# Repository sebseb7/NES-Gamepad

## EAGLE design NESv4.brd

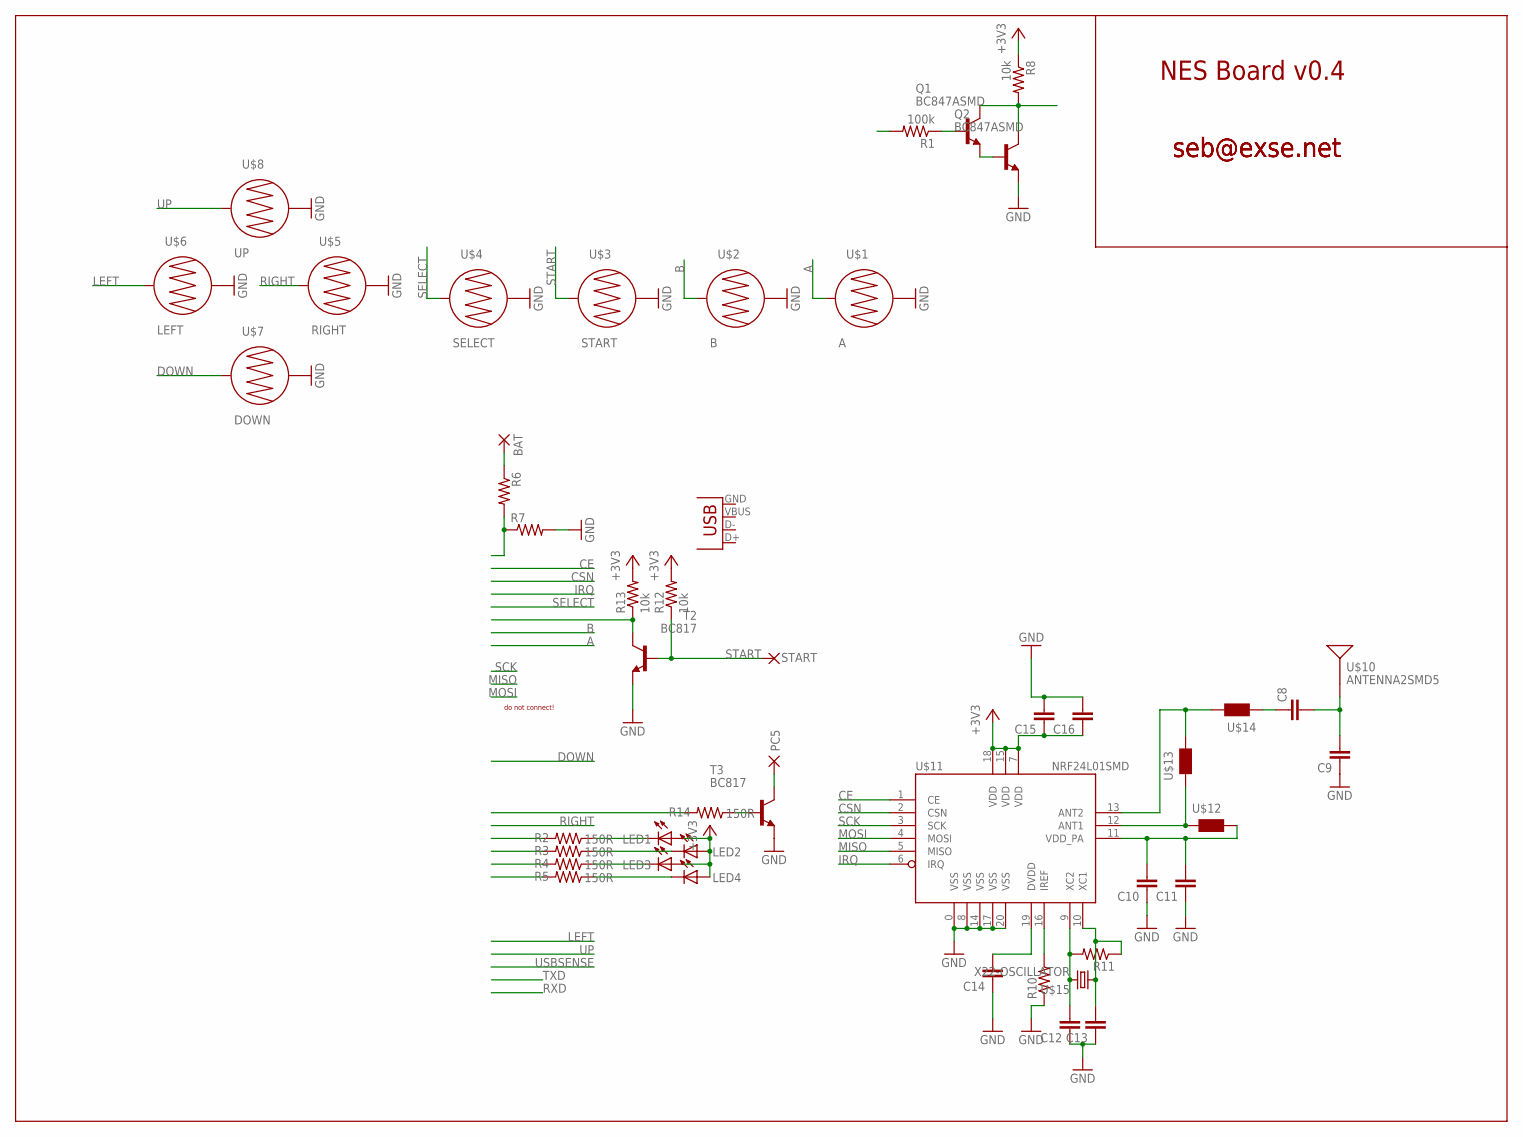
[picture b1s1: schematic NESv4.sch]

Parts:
BAT: SMD2; SMD1,27-2,54
C8, C9, C10, C11, C12, C13, C14, C15, C16: CAP0805; 0805
LED1, LED2, LED3, LED4: LED3MM
PC5: SMD2; SMD1,27-2,54
Q1, Q2: BC847ASMD; SOT23
R1: 100k; 0805
R2, R3, R4, R5, R14: 150R; 0805
R6, R7, R10, R11: RESISTOR; 0805
R8, R12, R13: 10k; 0805
START: SMD2; SMD1,27-2,54
T2, T3: BC817; SOT23
U$1: A; BUTTON-CONDUCTIVE
U$2: B; BUTTON-CONDUCTIVE
U$3: START; BUTTON-CONDUCTIVE
U$4: SELECT; BUTTON-CONDUCTIVE
U$5: RIGHT; BUTTON-CONDUCTIVE
U$6: LEFT; BUTTON-CONDUCTIVE
U$7: DOWN; BUTTON-CONDUCTIVE
U$8: UP; BUTTON-CONDUCTIVE
U$10: ANTENNA2SMD5; ANTENNA-CHIP5
U$11: NRF24L01SMD; QFN20
U$12, U$13, U$14: WE-KIHQ_0805; WE-KI_0805_B
U$15: X22-OSCILLATOR; X22
X1: USB-SMD-NS; USB-MINIB-NOSTOP

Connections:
+3V3: C15.1, C16.1, LED1.A, LED2.A, LED3.A, LED4.A, R8.1, R12.2, R13.2, U$11.7 (VDD), U$11.15 (VDD), U$11.18 (VDD)
A: U$1.1
B: U$2.1
CE: U$11.1 (CE)
CSN: U$11.2 (CSN)
DOWN: U$7.1
GND: C9.1, C10.1, C11.1, C12.1, C13.1, C14.1, C15.2, C16.2, Q2.2 (E), R7.2, R10.1, T2.2 (E), T3.2 (E), U$1.2, U$2.2, U$3.2, U$4.2, U$5.2, U$6.2, U$7.2, U$8.2, U$11.0 (VSS), U$11.8 (VSS), U$11.14 (VSS), U$11.17 (VSS), U$11.20 (VSS)
IRQ: U$11.6 (IRQ)
LEFT: U$6.1
MISO: U$11.5 (MISO)
MOSI: U$11.4 (MOSI)
unnamed: R14.1, T3.1 (B)
unnamed: Q1.2 (E), Q2.1 (B)
unnamed: LED1.K (C), R2.1
unnamed: LED2.K (C), R3.1
unnamed: LED3.K (C), R4.1
unnamed: LED4.K (C), R5.1
unnamed: R10.2, U$11.16 (IREF)
unnamed: Q1.1 (B), R1.1
unnamed: R6.2, R7.1
unnamed: BAT.1, R6.1
unnamed: Q1.3 (C), Q2.3 (C), R8.2
unnamed: R13.1, T2.3 (C)
unnamed: C13.2, R11.1, U$11.10 (XC1), U$15.1
unnamed: C12.2, R11.2, U$11.9 (XC2), U$15.3 (2)
unnamed: C10.2, C11.2, U$11.11 (VDD_PA), U$12.1 (2)
unnamed: U$11.12 (ANT1), U$12.2 (1), U$13.2 (1)
unnamed: U$11.13 (ANT2), U$13.1 (2), U$14.1 (2)
unnamed: C8.1, U$14.2 (1)
unnamed: C8.2, C9.2, U$10.FEED
unnamed: C14.2, U$11.19 (DVDD)
PC5: PC5.1, T3.3 (C)
RIGHT: U$5.1
SCK: U$11.3 (SCK)
SELECT: U$4.1
START: R12.1, START.1, T2.1 (B), U$3.1
UP: U$8.1

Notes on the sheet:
NES Board v0.4
seb@exse.net
do not connect!

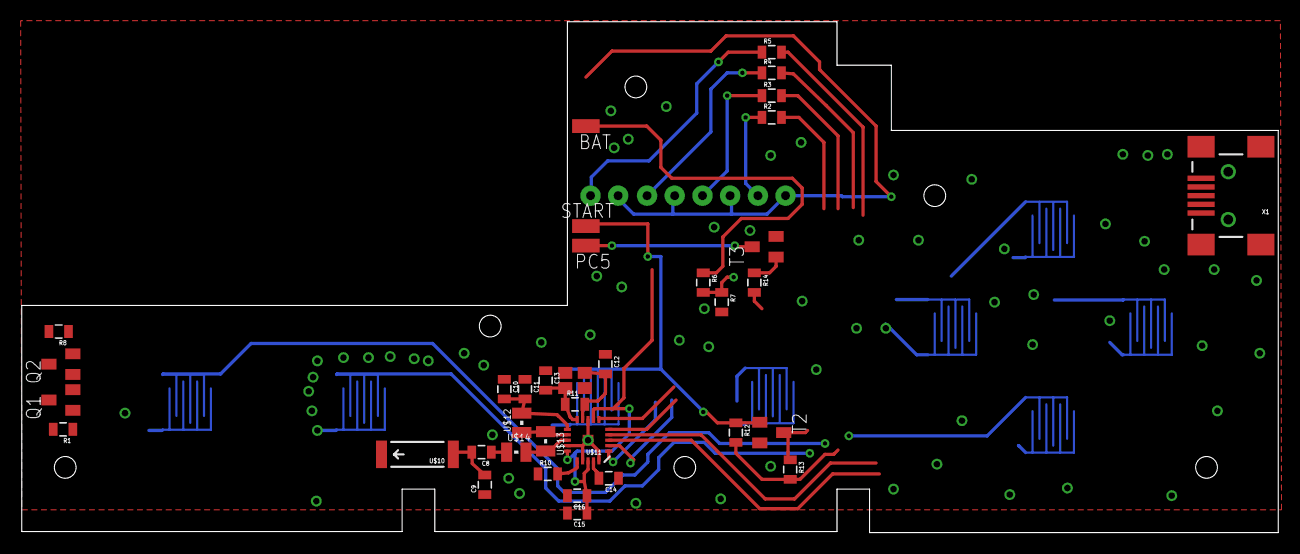
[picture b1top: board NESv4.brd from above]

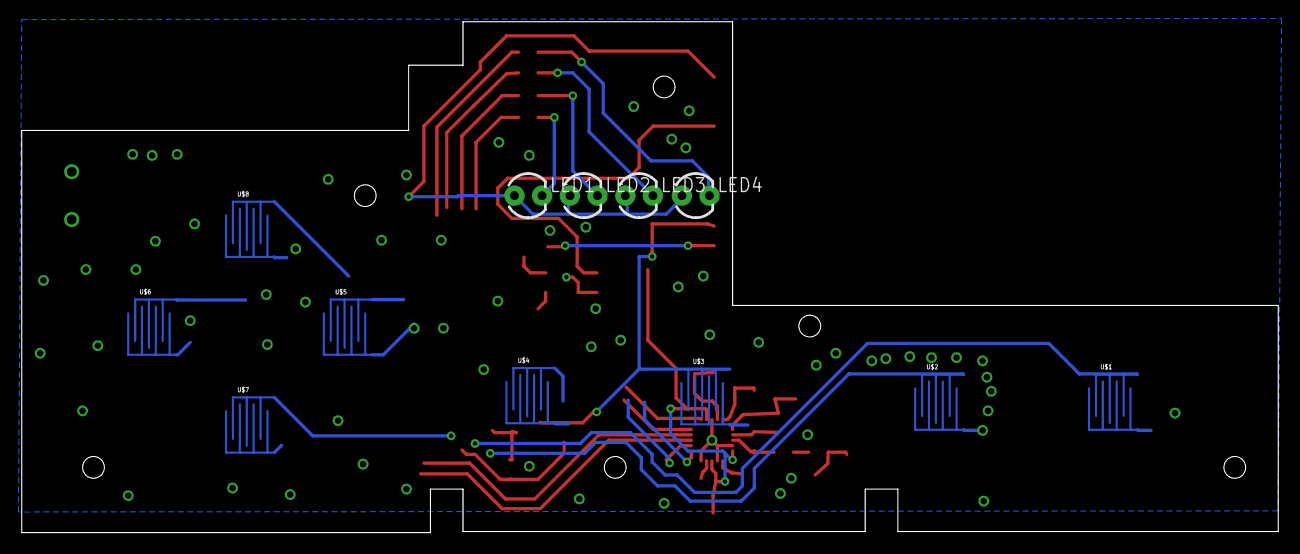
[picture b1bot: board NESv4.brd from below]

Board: 2 copper layers, 115.6 x 47.0 mm, 48 parts (12 on the bottom side), 24 nets.

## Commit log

2011-09-09 initial checkin
2011-09-09 removed eagle.epf file
2011-09-10 gitignore
2011-09-10 enabled brownout at 2.7
2011-10-11 path fixes
2011-10-19 power module , more routing done
2011-10-19 changes for v21
2011-12-06 final version for production
